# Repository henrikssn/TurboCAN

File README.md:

# TurboCAN

This is the official repository for the TurboCAN controller board, designed specifically for the [Voron AfterBurner] toolhead but can also be used on similar toolheads using NEMA17 steppers. The main benefit of this board is the capability to run the toolhead over just 4 wires (CAN, +24V, Ground) which greatly simplifies the wiring in the Voron v1 and v2 models.

[Voron AfterBurner]: https://github.com/VoronDesign/Voron-Afterburner

## Features

* 1x Combined CAN-bus and 24V power port with polarity protection
* 1x ADXL345 accelerometer for use with Klipper's input shaper feature
* 1x 24V stepper stick mount and motor output
* 3x 24V MOSFET fan0/fan1/heater outputs (up to 3A)
* 2x 5V powered endstop inputs (marked X/Y), could be used for toolhead mounted endstops (microswitch or hall effect), filament runout sensor or 5V Z probe.
* 1x 24V powered endstop input (marked Z) with built-in BAT42 diode, used for inductive probe on the AfterBurner but also supports microswitch based probing (e.g. Magprobe).
* 1x Thermistor input with 4.7k pullup resistor
* 1x USB-C port
* 1x SWD debug port with BOOT0/RESET broken out
* 5V 3A buck converter (available externally on X/Y endstops) and 3.3V 200mA linear regulator (internal only)
* Power LED & Activity (PA1) LED

The board supports interfacing with Klipper both over CAN and USB-C (selectable when building the Klipper firmware).

## Use cases

The TurboCAN board is actually not only useful as a toolhead board, here are some reasons why you want more of them:

* Want even less wiring? TurboCAN fits on the back of any NEMA17 stepper, so you can mount TurboCAN boards on e.g. the A/B (or X/Y) steppers and run them over a shared CAN bus.
* Need a USB to CAN interface? TurboCAN can do USB and CAN at the same time, so you can flash CandleLight firmware and use it as a USB-CAN interface.
* Want input shaper but annoyed by the complicated SPI wiring needed for the ADXL345 board? Just use a spare TurboCAN board over USB(/CAN) instead.

## Current status

**WARNING:** While the author has a working printer running a TurboCAN v0.1 board, this project is in early development, and most likely still has undiscovered issues. Build one at your own risk!

- [x] v0.1 boards ordered
- [x] v0.1 boards testing
  - [x] LEDs
  - [x] 3.3v LDO
  - [x] SWD debug port
  - [x] USB interface
  - [x] Buck converter
  - [x] Stepper stick
  - [x] MOSFET outputs
  - [x] CAN-bus + Flashing Klipper (CAN)
  - [x] Thermistor input
  - [x] X/Y endstop inputs
  - [x] Z endstop input

## Getting started

1. Configure Klipper using `make menuconfig`:

2. Put a jumper between `BOOT0` and `3.3V` and power cycle the board.

3. Flash the TurboCAN board using `make flash FLASH_DEVICE=1234:ABCD` (replace USB vendor/product, you find them with `lsusb`).

4. Connect the TurboCAN board using your favorite CAN bus interface (or use another TurboCAN board, see below).

5. Run the `klipper/scripts/canbus_query.py` command to determine the CAN address. See [Klipper docs](https://www.klipper3d.org/CANBUS.html) for more info.

6. Use the [provided Klipper config](klipper/turbocan.cfg) as a starting point.

## Changelog

### v0.2

* Errata fixes
  * LEDs are now mounted the right way.
  * R11 connected to R10/VSENSE.
  * SPI bus to the ADXL345 now have MISO/MOSI on the right pins.
  * Z probe input now has filtering and pullup resistor.
  * Reworked buck converter compensation circuitry.
  * Added CAN termination resistor.
* Added 100uF bulk capacitor for 24V to mitigate voltage fluctuations due to long cables.
* Thermistor resistor is now in 0805 package (was 0402) to simplify replacement to 1k (for PT1000 sensor).
* Improved filtering of analog power domain to reduce ADC noise.
* Replaced the heater mosfet with a more powerful AON7400A.
* Replaced the +3.3V connection to MS1 with an unpopulated resistor to give the board UART address 0 by default.
* Added optional pullup resistors to MS2/SPREAD to support standalone mode for the step stick.

## Errata

### v0.1

* LEDs are mounted backwards.
  * Workaround: Reverse them (or simply skip, they aren't essential).
* R11 not connected to R10/VSENSE.
  * Workaround: Simple to bodge as R10 is next to it.
* MISO and MOSI are swapped on the SPI bus to the ADXL345.
  * Workaround: Use software SPI.
* Z probe input lacks filtering and pullup resistor
  * Workaround: Use MCU internal pullup.
* Higher than optimal noise from the buck converter leading to noisy accelerometer readings.
  * Workaround: Doesn't need one, performance is still good enough for input shaper.
* No CAN termination resistors on-board
  * Workaround: Mount a 0603 120Ohm resistor between the H/L legs of the CAN JST-XH connector on each end of the bus.
* Thermistor readings are noisy (fluctuating 2-3C) with a PT1000 sensor
  * Workaround: Use a B3950 or replace the pullup resistor with a 1k 0.5%

## Developer Info

### Generating fabrication outputs for JLCPCB

1. Export Gerbers and drill file from pcbnew, make a zip file out of these.
2. Generate a BOM csv using `bom_csv_jlcpcb.py` from [kicad-jlcpcb-bom-plugin].
3. Generate a CPL file from pcbnew.
4. Convert the CPL file to JLCPCB format using  using `kicad_pos_to_cpl.py` from [kicad-jlcpcb-bom-plugin].

[kicad-jlcpcb-bom-plugin]: https://github.com/wokwi/kicad-jlcpcb-bom-plugin
## Attribution

Although this was designed from scratch, it was inspired by the [Huvud] board made by Pontus Borg.

[Huvud]: https://github.com/bondus/KlipperToolboard

## License

For compability with other Voron projects, all included files are licensed under the [GNU GPL-3 license].

[GNU GPL-3 license]: https://www.gnu.org/licenses/gpl-3.0.html

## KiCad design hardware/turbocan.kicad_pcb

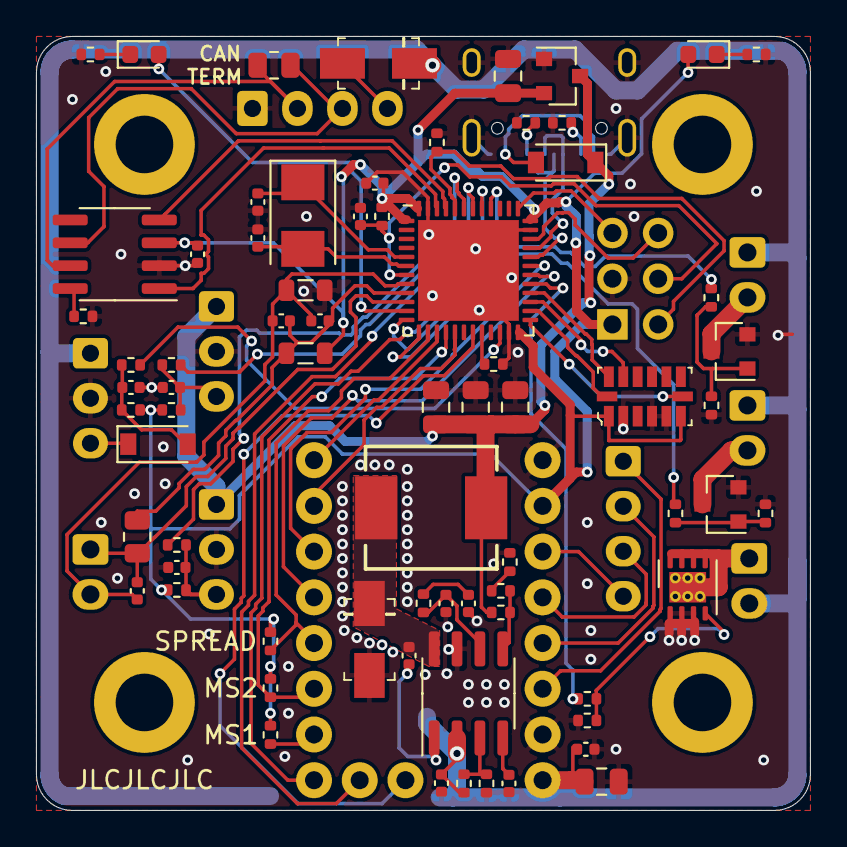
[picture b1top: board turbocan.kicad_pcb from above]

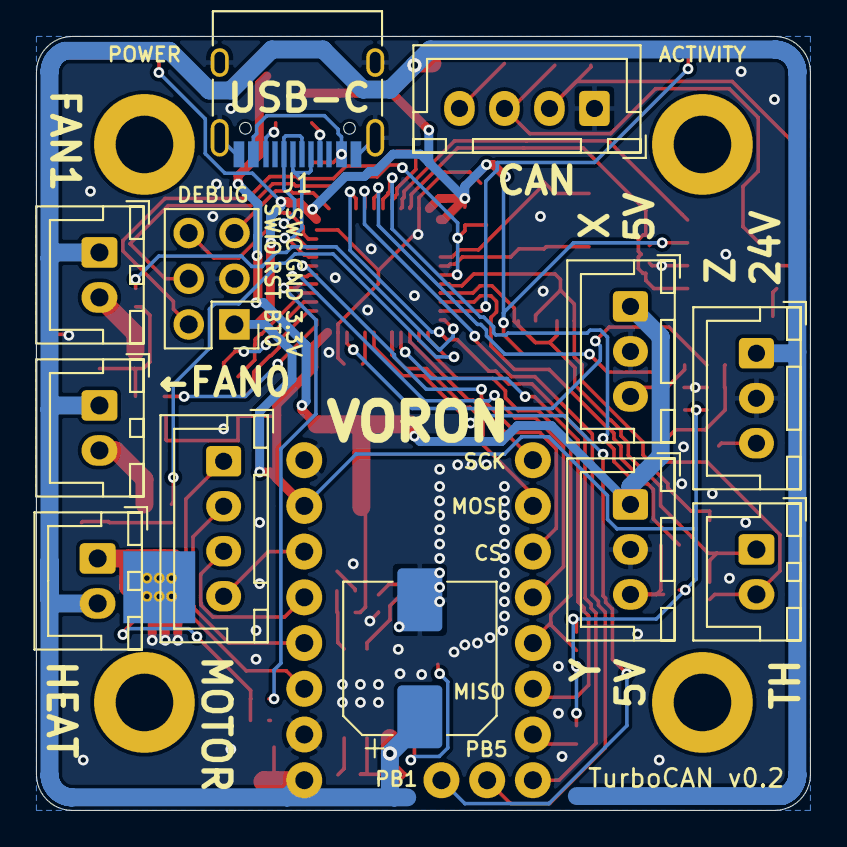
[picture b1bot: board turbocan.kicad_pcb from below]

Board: 2 copper layers, 43.0 x 43.0 mm, 88 parts (13 on the bottom side), 70 nets.

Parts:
C1, C5: 10uF; C_0805_2012Metric
C2, C3, C4, C9, C10, C11, C12, C17, C20, C22: 100nF; C_0402_1005Metric
C6, C19: 10nF; C_0402_1005Metric
C7: 1nF; C_0402_1005Metric
C8: 1pF; C_0402_1005Metric
C13, C14, C15: 22uF; C_0805_2012Metric
C16, C18: 12pF; C_0402_1005Metric
C21: 100uF; CP_Elec_8x10
C23: 1uF; C_0402_1005Metric
D1: BAT42W-V; D_SOD-123
D2, D3: SS54; DO-214AC
D4: BAT42W; D_SOD-123
D5: LED_Red; LED_0603_1608Metric
D6: LED_Green; LED_0603_1608Metric
H1, H2, H3, H4: MountingHole; MountingHole_3.2mm_M3_DIN965_Pad
J1: USB_C_Receptacle_USB2.0; USB_C_Receptacle_HRO_TYPE-C-31-M-12
J2: STEPPER; JST_XH_B4B-XH-A_1x04_P2.50mm_Vertical
J5: DEBUG; PinHeader_2x03_P2.54mm_Vertical
J7: ENDSTOPX; JST_XH_B3B-XH-A_1x03_P2.50mm_Vertical
J8: ENDSTOPY; JST_XH_B3B-XH-A_1x03_P2.50mm_Vertical
J9: TH0; JST_XH_B2B-XH-A_1x02_P2.50mm_Vertical
J10: CAN_PORT; JST_XH_B4B-XH-A_1x04_P2.50mm_Vertical
J11: FAN0; JST_XH_B2B-XH-A_1x02_P2.50mm_Vertical
J12: FAN1; JST_XH_B2B-XH-A_1x02_P2.50mm_Vertical
J13: HEAT; JST_XH_B2B-XH-A_1x02_P2.50mm_Vertical
J14: PROBE; JST_XH_B3B-XH-A_1x03_P2.50mm_Vertical
L1: 6.8uH; L_SMD_7.3x6.8
L2, L3: Ferrite bead; L_0805_2012Metric
R1, R2: 5.1k; R_0402_1005Metric
R3, R12, R13, R23, R24, R28: 1k; R_0402_1005Metric
R4: 330k; R_0402_1005Metric
R5, R6: 68k; R_0402_1005Metric
R7, R8, R10, R14, R15, R16, R20, R21, R22, R27: 10k; R_0402_1005Metric
R9: 4.7k; R_0805_2012Metric
R11: 1.2k; R_0402_1005Metric
R17, R18, R19: 100; R_0402_1005Metric
R25: 680; R_0402_1005Metric
R26: 120Ohm; R_0805_2012Metric
R29, R30, R31: DNP; R_0402_1005Metric
U1: AP2127N-3.3; SOT-23
U2: TMC2209StepStick
U3: SN65HVD230; SOIC-8_3.9x4.9mm_P1.27mm
U4: TPS54331; SOIC-8_3.9x4.9mm_P1.27mm
U5, U6: AO3400A; SOT-23
U7: AON7400A; DFN-8-1EP_3x3mm_P0.65mm_EP1.7x2.05mm_Thermal_Pad
U8: STM32F072CBUx; QFN-48-1EP_7x7mm_P0.5mm_EP5.6x5.6mm
U9: ADXL345BCCZ; LGA-14_3x5mm_RevA
Y1: Crystal; Crystal_SMD_5032-2Pin_5.0x3.2mm

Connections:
+3V3: C1.1, C3.1, C22.2, D6.2, J5.1, L2.1, R7.1, R8.1, R20.1, R27.1, R29.1, R30.1, R31.1, U1.2, U2.2, U3.3, U8.1, U8.24, U8.36, U8.48, U9.1, U9.6
+5V: C13.1, C14.1, C15.1, D1.1, J7.1, J8.1, L1.2, R10.1, U1.3
+24V: C2.2, C4.1, C5.1, C21.1, D2.K, J11.1, J12.1, J13.2, J14.1, R4.1, U2.8, U4.2
/SWITCH: C9.1, D3.K, L1.1, U4.8
A_CS: U8.25, U9.7
A_MISO: U8.27, U9.12
A_MOSI: U8.28, U9.13
A_SCK: U8.26, U9.14
BOOT0: J5.2, R21.1, U8.44
BOOT1: R22.1, U8.20
CANH: J10.2, R26.1, U3.7
CANL: J10.3, R26.2, U3.6
CANRX: U3.4, U8.45
CANTX: U3.1, U8.46
CS_RX: U2.11, U8.31
DIAG: U2.18, U8.41
EN: U2.16, U8.40
ENDSTOPX: R12.1, U8.42
ENDSTOPY: R13.1, U8.43
FAN0: R17.1, U8.12
FAN1: R18.1, U8.13
GND: C1.2, C2.1, C3.2, C4.2, C5.2, C6.2, C7.2, C8.2, C10.2, C11.2, C13.2, C14.2, C15.2, C16.2, C17.2, C18.2, C20.2, C21.2, C22.1, D3.A, J1.A1, J1.A12, J1.B1, J1.B12, J1.S1, J5.3, J7.2, J8.2, J10.1, J14.2, L3.1, R1.2, R2.2, R3.2, R5.2, R14.2, R15.2, R16.2, R21.2, R22.2, R23.2, R24.2, R25.2, U1.1, U2.1, U2.7, U3.2, U4.7, U5.2, U6.2, U7.1, U8.23, U8.35, U8.47, U8.49, U9.2, U9.4, U9.5
GNDA: C12.2, C19.2, C23.2, J9.2, L3.2, U8.8
HEAT: R19.1, U8.29
INDEX: U2.17, U8.19
INT1_TX: U2.12, U8.30
INT2: R31.2, U2.13, U8.14
LED: D5.2, U8.11
MISO: R30.2, U2.14, U8.16
MOSI_STEP: U2.10, U8.17
NRST: C17.1, J5.4, R20.2, U8.7
unnamed: C6.1, U4.4
unnamed: C7.1, R6.2
unnamed: C8.1, R6.1, U4.6
unnamed: C9.2, U4.1
unnamed: C10.1, J7.3, R7.2, R12.2
unnamed: C11.1, J8.3, R8.2, R13.2
unnamed: C20.1, D4.2, R27.2, R28.2
unnamed: D1.2, J1.A4, J1.A9, J1.B4, J1.B9
unnamed: D2.A, J10.4
unnamed: D4.1, J14.3
unnamed: D5.1, R23.1
unnamed: D6.1, R24.1
unnamed: J1.A5, R1.1
unnamed: J1.B5, R2.1
unnamed: J2.1, U2.6
unnamed: J2.2, U2.5
unnamed: J2.3, U2.4
unnamed: J2.4, U2.3
unnamed: J11.2, U5.3
unnamed: J12.2, U6.3
unnamed: J13.1, U7.3
unnamed: R3.1, U3.8
unnamed: R4.2, R5.1, U4.3
unnamed: R10.2, R11.1, U4.5
unnamed: R11.2, R25.1
unnamed: R14.1, R17.2, U5.1
unnamed: R15.1, R18.2, U6.1
unnamed: R16.1, R19.2, U7.2
unnamed: R29.2, U2.15
PROBEZ: R28.1, U8.22
SCK_DIR: U2.9, U8.15
SWCLK: J5.5, U8.37
SWDIO: J5.6, U8.34
TH0: C12.1, J9.1, R9.2, U8.10
USBDM: J1.A7, J1.B7, U8.32
USBDP: J1.A6, J1.B6, U8.33
VDDA: C19.1, C23.1, L2.2, R9.1, U8.9
XTAL0: C16.1, U8.5, Y1.1
XTAL1: C18.1, U8.6, Y1.2

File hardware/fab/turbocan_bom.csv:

Comment,Designator,Footprint,LCSC Part #
10uF ,"C1,C5",C_0805_2012Metric,C15850
100nF ,"C2,C3,C4,C9,C10,C11,C12,C17,C20,C22",C_0402_1005Metric,C1525
10nF ,"C6,C19",C_0402_1005Metric,C15195
1nF ,C7,C_0402_1005Metric,C1523
1pF ,C8,C_0402_1005Metric,C1550
22uF ,"C13,C14,C15",C_0805_2012Metric,C45783
12pF ,"C16,C18",C_0402_1005Metric,C1547
100uF ,C21,CP_Elec_8x10,C59944
1uF ,C23,C_0402_1005Metric,C52923
BAT42W-V ,D1,D_SOD-123,C8598
SS54 ,"D2,D3",DO-214AC,C22452
BAT42W ,D4,D_SOD-123,C8598
LED_Red ,D5,LED_0603_1608Metric,C2286
LED_Green ,D6,LED_0603_1608Metric,C72043
MountingHole ,"H1,H2,H3,H4",MountingHole_3.2mm_M3_DIN965_Pad,
USB_C_Receptacle_USB2.0 ,J1,USB_C_Receptacle_HRO_TYPE-C-31-M-12,
STEPPER ,J2,JST_XH_B4B-XH-A_1x04_P2.50mm_Vertical,
DEBUG ,J5,PinHeader_2x03_P2.54mm_Vertical,
ENDSTOPX ,J7,JST_XH_B3B-XH-A_1x03_P2.50mm_Vertical,
ENDSTOPY ,J8,JST_XH_B3B-XH-A_1x03_P2.50mm_Vertical,
TH0 ,J9,JST_XH_B2B-XH-A_1x02_P2.50mm_Vertical,
CAN_PORT ,J10,JST_XH_B4B-XH-A_1x04_P2.50mm_Vertical,
FAN0 ,J11,JST_XH_B2B-XH-A_1x02_P2.50mm_Vertical,
FAN1 ,J12,JST_XH_B2B-XH-A_1x02_P2.50mm_Vertical,
HEAT ,J13,JST_XH_B2B-XH-A_1x02_P2.50mm_Vertical,
PROBE ,J14,JST_XH_B3B-XH-A_1x03_P2.50mm_Vertical,
6.8uH ,L1,L_SMD_7.3x6.8,C207841
Ferrite bead ,"L2,L3",L_0805_2012Metric,C1017
5.1k ,"R1,R2",R_0402_1005Metric,C25905
1k ,"R3,R12,R13,R23,R24,R28",R_0402_1005Metric,C11702
330k ,R4,R_0402_1005Metric,C25778
68k ,"R5,R6",R_0402_1005Metric,C36871
10k ,"R7,R8,R10,R14,R15,R16,R20,R21,R22,R27",R_0402_1005Metric,C25744
4.7k ,R9,R_0805_2012Metric,C17673
1.2k ,R11,R_0402_1005Metric,C25862
100 ,"R17,R18,R19",R_0402_1005Metric,C25076
680 ,R25,R_0402_1005Metric,C25130
120Ohm ,R26,R_0805_2012Metric,C17437
DNP ,"R29,R30,R31",R_0402_1005Metric,
AP2127N-3.3 ,U1,SOT-23,C5446
TMC2209StepStick ,U2,TMC2209StepStick,
SN65HVD230 ,U3,SOIC-8_3.9x4.9mm_P1.27mm,C12084
TPS54331 ,U4,SOIC-8_3.9x4.9mm_P1.27mm,C9865
AO3400A ,"U5,U6",SOT-23,C344010
AON7400A ,U7,DFN-8-1EP_3x3mm_P0.65mm_EP1.7x2.05mm,C85734
STM32F072CBUx ,U8,QFN-48-1EP_7x7mm_P0.5mm_EP5.6x5.6mm,C92504
ADXL345BCCZ ,U9,LGA-14_3x5mm_RevA,C9667
Crystal ,Y1,Crystal_SMD_5032-2Pin_5.0x3.2mm,C115962

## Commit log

2021-06-08 Public release
2021-06-22 Make the KiCAD files standalone
2021-06-22 Replace heater mosfet
2021-06-23 Fix typo in README
2021-06-23 Replace pullup on MS1 with unpopulated resistor
2021-06-23 Also add optional pullup resistors on MS2 and SPREAD
2021-06-30 Fix orientation of LEDs/C21 and update C8 to 1pF
2021-06-30 Regenerate fabrication outputs
2021-07-05 Swap drain and source on heater MOSFET.
2021-07-06 Move AON7400A labels to outside of symbol
2021-07-06 Regenerate fabrication files
2021-07-08 Add thermal pad and vias for heater MOSFET.
